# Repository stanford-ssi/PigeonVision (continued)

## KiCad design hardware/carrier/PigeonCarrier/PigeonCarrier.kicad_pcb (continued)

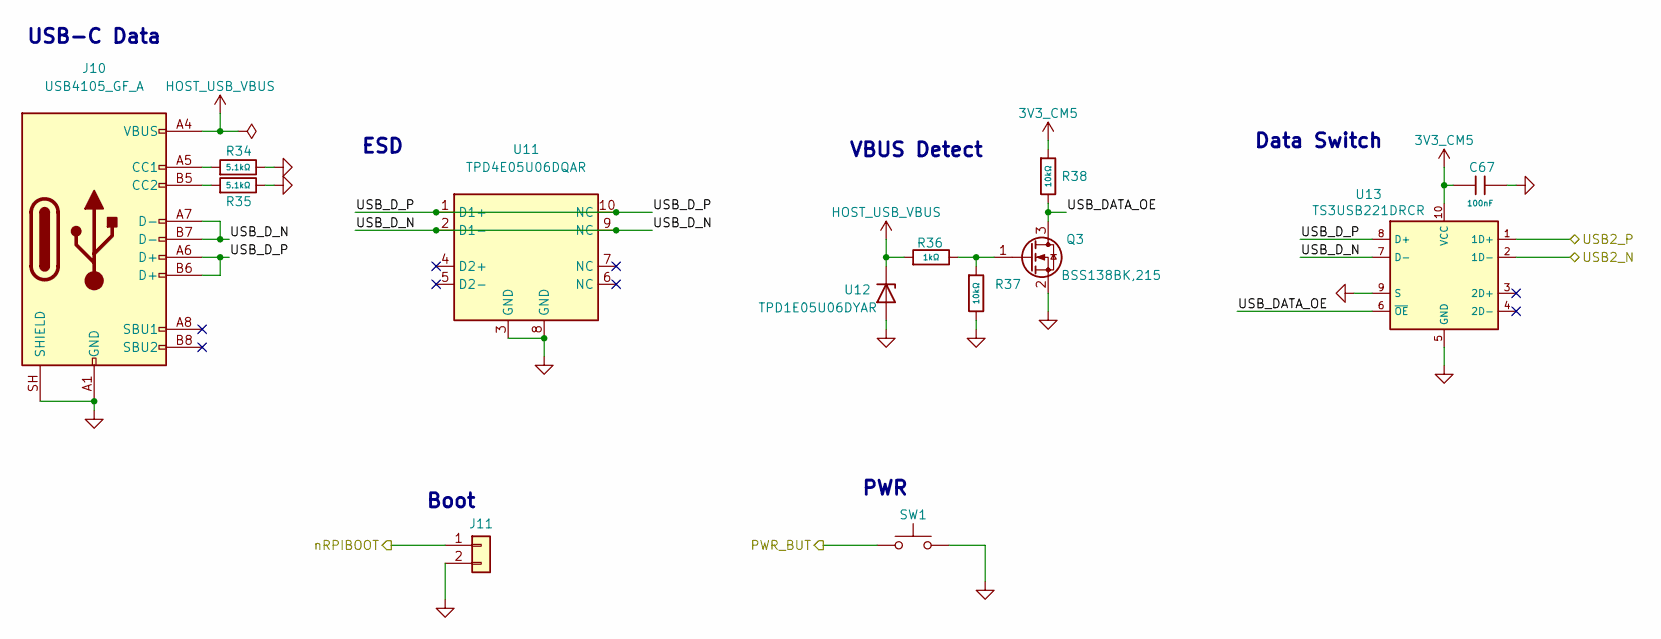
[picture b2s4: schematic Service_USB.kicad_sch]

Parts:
C67: 100nF; C_0402; Voltage Rated 50V; Tolerance ±10%; Part CL05B104KB54PNC; LCSC C307331
J10: USB4105_GF_A; USB_C_Receptacle_GCT_USB4105_GF_A_16P; MPN USB4105-GF-A; DigiKey Part Number 2073-USB4105-GF-ACT-ND
J11: Samtec_TSM-102-01-L-SV-P-TR; Samtec_TSM-102-01_SV_1x02_P2.54mm_SMD; MPN TSM-102-01-L-SV-P-TR; DigiKey Part Number 612-TSM-102-01-L-SV-P-TRCT-ND
Q3: BSS138BK,215; Nexperia_SOT23_BSS138BK; MPN BSS138BK,215; DigiKey Part Number 1727-1141-1-ND
R34, R35: 5.1kΩ; R_0402; Overload Voltage (Max) 50V; Tolerance ±1%; Part 0402WGF5101TCE; LCSC C25905
R36: 1kΩ; R_0402; Overload Voltage (Max) 50V; Tolerance ±1%; Part 0402WGF1001TCE; LCSC C11702
R37, R38: 10kΩ; R_0402; Overload Voltage (Max) 50V; Tolerance ±1%; Part 0402WGF1002TCE; LCSC C25744
SW1: PTS636 SK25 SMTR LFS; CK_PTS636_SK25_SMTR_LFS_GullWing_SMD; MPN PTS636 SK25 SMTR LFS; LCSC C2689642
U11: TPD4E05U06DQAR; TI_DQA0010A_USON-10_1x2.5mm_P0.5mm; MPN TPD4E05U06DQAR; LCSC Part # C138714
U12: TPD1E05U06DYAR; TI_DYA0002A_SOD523_TPD1E05U06; MPN TPD1E05U06DYAR; DigiKey Part # 296-TPD1E05U06DYARCT-ND
U13: TS3USB221DRCR; TI_DRC0010J_VSON-10_3x3mm_P0.5mm; MPN TS3USB221DRCR; DigiKey Part Number 296-21360-1-ND

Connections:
3V3_CM5: C67.1, R38.1, U13.10 (VCC); also elsewhere on the board
/CM5/PWR_BUT: SW1.1; also elsewhere on the board
/CM5/USB2_N: U13.2 (1D-); also elsewhere on the board
/CM5/USB2_P: U13.1 (1D+); also elsewhere on the board
/CM5/nRPIBOOT: J11.1; also elsewhere on the board
/USB & Service/USB_DATA_OE: Q3.3 (D), R38.2, U13.6 (~OE)
/USB & Service/USB_D_N: J10.A7 (D-), J10.B7 (D-), U11.2 (D1-), U11.9 (NC), U13.7 (D-)
/USB & Service/USB_D_P: J10.A6 (D+), J10.B6 (D+), U11.1 (D1+), U11.10 (NC), U13.8 (D+)
GND: C67.2, J10.A1 (GND), J10.A12 (GND), J10.B1 (GND), J10.B12 (GND), J10.SH (SHIELD), J11.2, Q3.2 (S), R34.2, R35.2, R37.2, SW1.2, U11.3 (GND), U11.8 (GND), U12.2 (GND), U13.5 (GND), U13.9 (S), U13.11 (EP); also elsewhere on the board
HOST_USB_VBUS: J10.A4 (VBUS), J10.A9 (VBUS), J10.B4 (VBUS), J10.B9 (VBUS), R36.1, U12.1 (I/O)
unnamed: J10.A5 (CC1), R34.1
unnamed: J10.B5 (CC2), R35.1
unnamed: Q3.1 (G), R36.2, R37.1

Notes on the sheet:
VBUS Detect
Data Switch
USB-C Data
Boot
PWR
ESD

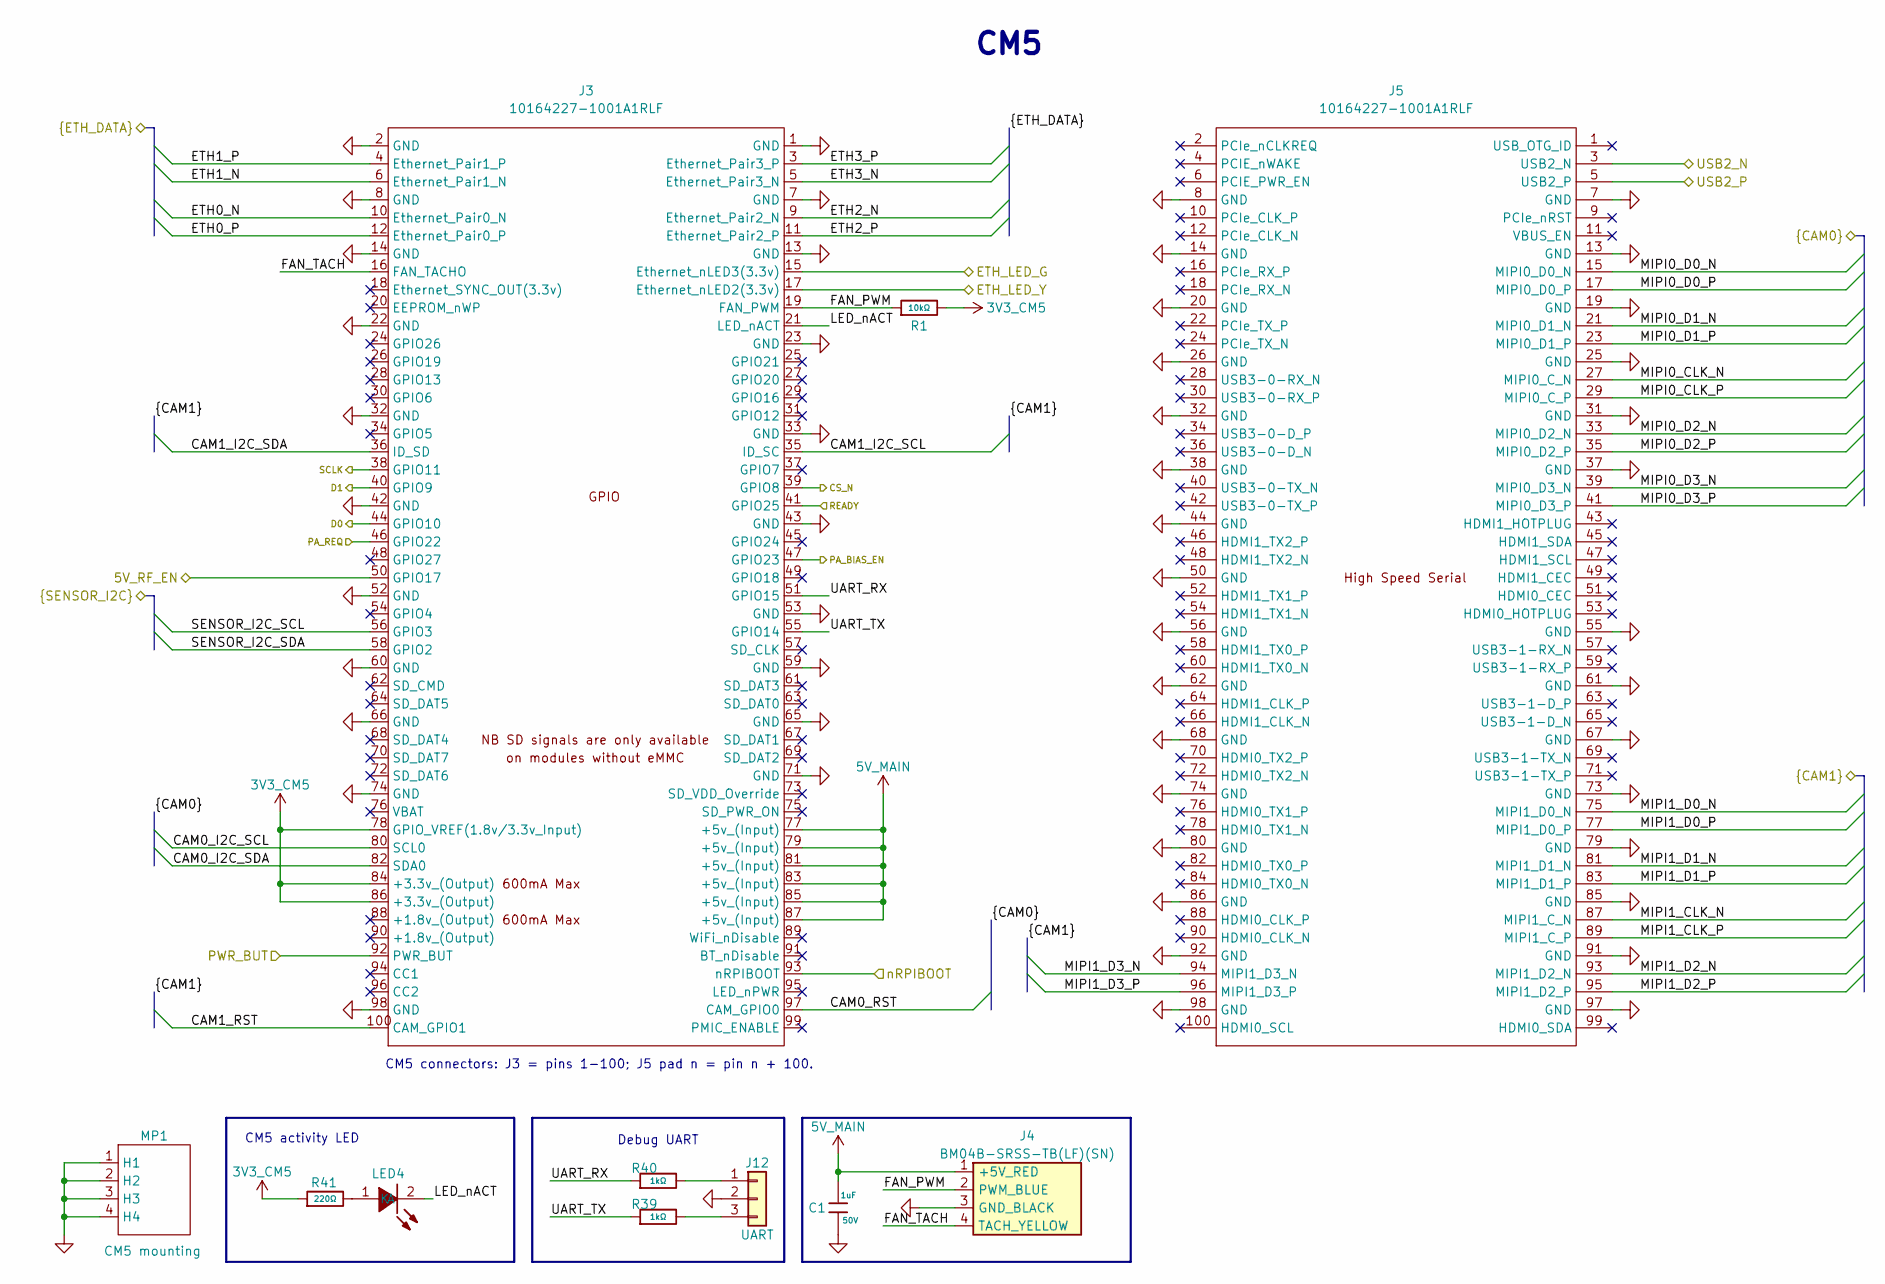
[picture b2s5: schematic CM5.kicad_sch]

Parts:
C1: 1uF; C_0805; Voltage Rated 50V; Tolerance ±10%; Part CL21B105KBFNNNE; LCSC C28323
J3: 10164227-1001A1RLF; Amphenol_10164227-1001A1RLF_2x50_P0.40mm; MPN 10164227-1001A1RLF; LCSC C6782225
J4: BM04B-SRSS-TB(LF)(SN); JST_SH_BM04B-SRSS-TB_1x04-1MP_P1.00mm_Vertical; MPN BM04B-SRSS-TB(LF)(SN); LCSC Part # C160390
J5: 10164227-1001A1RLF; Amphenol_10164227-1001A1RLF_2x50_P0.40mm_CM5_J2; MPN 10164227-1001A1RLF; LCSC C6782225
J12: UART; JST_SH_BM03B-SRSS-TB_1x03-1MP_P1.00mm_Vertical; MPN BM03B-SRSS-TB(LF)(SN); LCSC C160389
LED4: 0805G_Green; Manufacturer Part KT-0805G; LCSC C2297
MP1: CM5 mounting; CM5_Mounting_55x40mm
R1: 10kΩ; R_0402; Overload Voltage (Max) 50V; Tolerance ±1%; Part 0402WGF1002TCE; LCSC C25744
R39, R40: 1kΩ; R_0402; Overload Voltage (Max) 50V; Tolerance ±1%; Part 0402WGF1001TCE; LCSC C11702
R41: 220Ω; R_0402; Overload Voltage (Max) 50V; Tolerance ±1%; Part 0402WGF2200TCE; LCSC C25091

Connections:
3V3_CM5: J3.78 (GPIO_VREF(1.8v/3.3v_Input)), J3.84 (+3.3v_(Output)), J3.86 (+3.3v_(Output)), R1.2, R41.1; also elsewhere on the board
5V_MAIN: C1.1, J3.77 (+5v_(Input)), J3.79 (+5v_(Input)), J3.81 (+5v_(Input)), J3.83 (+5v_(Input)), J3.85 (+5v_(Input)), J3.87 (+5v_(Input)), J4.1 (+5V_RED); also elsewhere on the board
/CM5/5V_RF_EN: J3.50 (GPIO17); also elsewhere on the board
/CM5/CAM0_I2C_SCL: J3.80 (SCL0); also elsewhere on the board
/CM5/CAM0_I2C_SDA: J3.82 (SDA0); also elsewhere on the board
/CM5/CAM0_RST: J3.97 (CAM_GPIO0); also elsewhere on the board
/CM5/CAM1_I2C_SCL: J3.35 (ID_SC); also elsewhere on the board
/CM5/CAM1_I2C_SDA: J3.36 (ID_SD); also elsewhere on the board
/CM5/CAM1_RST: J3.100 (CAM_GPIO1); also elsewhere on the board
/CM5/CS_N: J3.39 (GPIO8); also elsewhere on the board
/CM5/D0: J3.44 (GPIO10); also elsewhere on the board
/CM5/D1: J3.40 (GPIO9); also elsewhere on the board
/CM5/ETH0_N: J3.10 (Ethernet_Pair0_N); also elsewhere on the board
/CM5/ETH0_P: J3.12 (Ethernet_Pair0_P); also elsewhere on the board
/CM5/ETH1_N: J3.6 (Ethernet_Pair1_N); also elsewhere on the board
/CM5/ETH1_P: J3.4 (Ethernet_Pair1_P); also elsewhere on the board
/CM5/ETH2_N: J3.9 (Ethernet_Pair2_N); also elsewhere on the board
/CM5/ETH2_P: J3.11 (Ethernet_Pair2_P); also elsewhere on the board
/CM5/ETH3_N: J3.5 (Ethernet_Pair3_N); also elsewhere on the board
/CM5/ETH3_P: J3.3 (Ethernet_Pair3_P); also elsewhere on the board
/CM5/ETH_LED_G: J3.15 (Ethernet_nLED3(3.3v)); also elsewhere on the board
/CM5/ETH_LED_Y: J3.17 (Ethernet_nLED2(3.3v)); also elsewhere on the board
/CM5/FAN_PWM: J3.19 (FAN_PWM), J4.2 (PWM_BLUE), R1.1
/CM5/FAN_TACH: J3.16 (FAN_TACHO), J4.4 (TACH_YELLOW)
/CM5/LED_nACT: J3.21 (LED_nACT), LED4.2 (K)
/CM5/MIPI0_CLK_N: J5.27 (MIPI0_C_N); also elsewhere on the board
/CM5/MIPI0_CLK_P: J5.29 (MIPI0_C_P); also elsewhere on the board
/CM5/MIPI0_D0_N: J5.15 (MIPI0_D0_N); also elsewhere on the board
/CM5/MIPI0_D0_P: J5.17 (MIPI0_D0_P); also elsewhere on the board
/CM5/MIPI0_D1_N: J5.21 (MIPI0_D1_N); also elsewhere on the board
/CM5/MIPI0_D1_P: J5.23 (MIPI0_D1_P); also elsewhere on the board
/CM5/MIPI0_D2_N: J5.33 (MIPI0_D2_N); also elsewhere on the board
/CM5/MIPI0_D2_P: J5.35 (MIPI0_D2_P); also elsewhere on the board
/CM5/MIPI0_D3_N: J5.39 (MIPI0_D3_N); also elsewhere on the board
/CM5/MIPI0_D3_P: J5.41 (MIPI0_D3_P); also elsewhere on the board
/CM5/MIPI1_CLK_N: J5.87 (MIPI1_C_N); also elsewhere on the board
/CM5/MIPI1_CLK_P: J5.89 (MIPI1_C_P); also elsewhere on the board
/CM5/MIPI1_D0_N: J5.75 (MIPI1_D0_N); also elsewhere on the board
/CM5/MIPI1_D0_P: J5.77 (MIPI1_D0_P); also elsewhere on the board
/CM5/MIPI1_D1_N: J5.81 (MIPI1_D1_N); also elsewhere on the board
/CM5/MIPI1_D1_P: J5.83 (MIPI1_D1_P); also elsewhere on the board
/CM5/MIPI1_D2_N: J5.93 (MIPI1_D2_N); also elsewhere on the board
/CM5/MIPI1_D2_P: J5.95 (MIPI1_D2_P); also elsewhere on the board
/CM5/MIPI1_D3_N: J5.94 (MIPI1_D3_N); also elsewhere on the board
/CM5/MIPI1_D3_P: J5.96 (MIPI1_D3_P); also elsewhere on the board
/CM5/PA_REQ: J3.46 (GPIO22); also elsewhere on the board
/CM5/PWR_BUT: J3.92 (PWR_BUT); also elsewhere on the board
/CM5/READY: J3.41 (GPIO25); also elsewhere on the board
/CM5/SCLK: J3.38 (GPIO11); also elsewhere on the board
/CM5/UART_RX: J3.51 (GPIO15), R40.1
/CM5/UART_TX: J3.55 (GPIO14), R39.1
/CM5/USB2_N: J5.3 (USB2_N); also elsewhere on the board
/CM5/USB2_P: J5.5 (USB2_P); also elsewhere on the board
/CM5/nRPIBOOT: J3.93 (nRPIBOOT); also elsewhere on the board
/PA_BIAS_EN: J3.47 (GPIO23); also elsewhere on the board
/Sensors/SENSOR_I2C_SCL: J3.56 (GPIO3); also elsewhere on the board
/Sensors/SENSOR_I2C_SDA: J3.58 (GPIO2); also elsewhere on the board
GND: C1.2, J3.1 (GND), J3.2 (GND), J3.7 (GND), J3.8 (GND), J3.13 (GND), J3.14 (GND), J3.22 (GND), J3.23 (GND), J3.32 (GND), J3.33 (GND), J3.42 (GND), J3.43 (GND), J3.52 (GND), J3.53 (GND), J3.59 (GND), J3.60 (GND), J3.65 (GND), J3.66 (GND), J3.71 (GND), J3.74 (GND), J3.98 (GND), J4.3 (GND_BLACK), J5.7 (GND), J5.8 (GND), J5.13 (GND), J5.14 (GND), J5.19 (GND), J5.20 (GND), J5.25 (GND), J5.26 (GND), J5.31 (GND), J5.32 (GND), J5.37 (GND), J5.38 (GND), J5.44 (GND), J5.50 (GND), J5.55 (GND), J5.56 (GND), J5.61 (GND), J5.62 (GND), J5.67 (GND), J5.68 (GND), J5.73 (GND), J5.74 (GND), J5.79 (GND), J5.80 (GND), J5.85 (GND), J5.86 (GND), J5.91 (GND), J5.92 (GND), J5.97 (GND), J5.98 (GND), J12.2, MP1.1 (H1), MP1.2 (H2), MP1.3 (H3), MP1.4 (H4); also elsewhere on the board
unnamed: J12.1, R40.2
unnamed: J12.3, R39.2
unnamed: LED4.1 (A), R41.2

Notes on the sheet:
Debug UART
CM5
CM5 connectors: J3 = pins 1-100; J5 pad n = pin n + 100.
CM5 activity LED

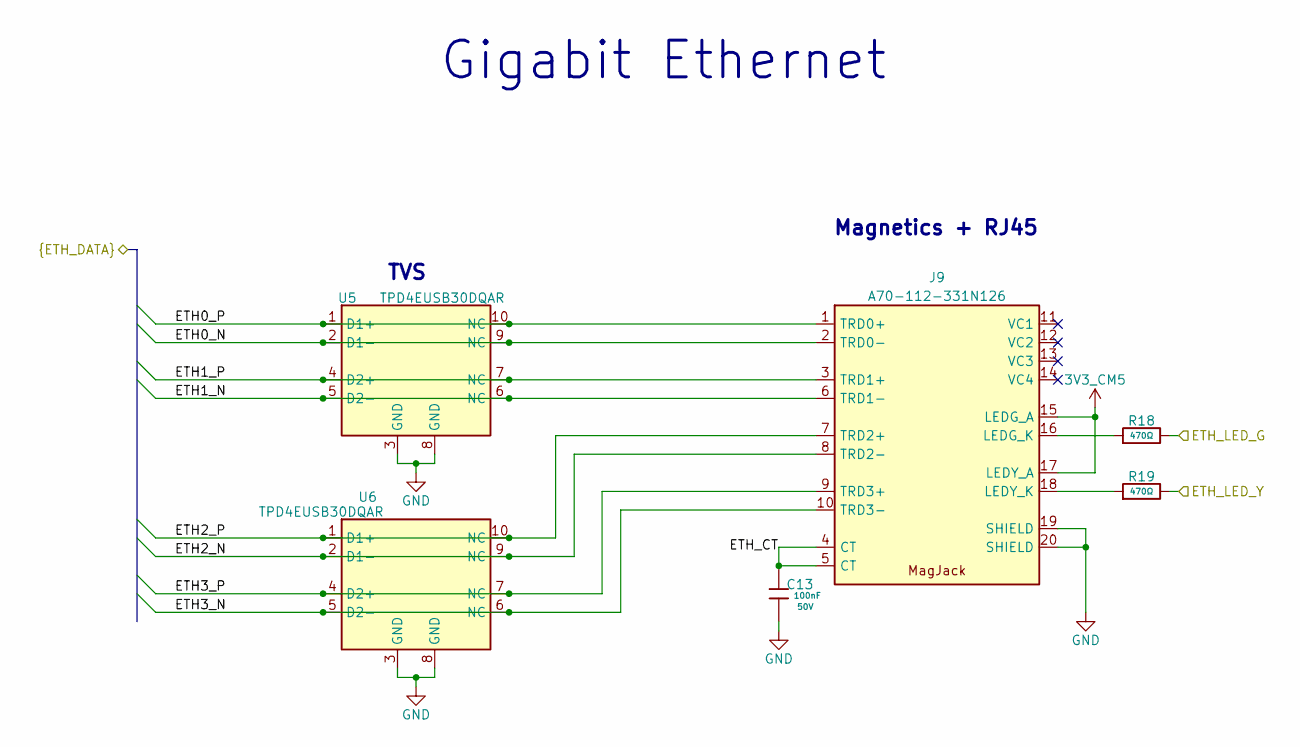
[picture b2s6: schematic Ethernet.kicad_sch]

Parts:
C13: 100nF; C_0402; Voltage Rated 50V; Tolerance ±10%; Part CL05B104KB54PNC; LCSC C307331
J9: A70-112-331N126; RJ45_EDAC_A70-112-331N126; MPN A70-112-331N126; LCSC Part # C43709820
R18, R19: 470Ω; R_0402; Overload Voltage (Max) 50V; Tolerance ±1%; Part 0402WGF4700TCE; LCSC C25117
U5, U6: TPD4EUSB30DQAR; TI_DQA0010A_USON-10_1x2.5mm_P0.5mm; MPN TPD4EUSB30DQAR; LCSC Part # C90627

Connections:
3V3_CM5: J9.15 (LEDG_A), J9.17 (LEDY_A); also elsewhere on the board
/CM5/ETH0_N: J9.2 (TRD0-), U5.2 (D1-), U5.9 (NC); also elsewhere on the board
/CM5/ETH0_P: J9.1 (TRD0+), U5.1 (D1+), U5.10 (NC); also elsewhere on the board
/CM5/ETH1_N: J9.6 (TRD1-), U5.5 (D2-), U5.6 (NC); also elsewhere on the board
/CM5/ETH1_P: J9.3 (TRD1+), U5.4 (D2+), U5.7 (NC); also elsewhere on the board
/CM5/ETH2_N: J9.8 (TRD2-), U6.2 (D1-), U6.9 (NC); also elsewhere on the board
/CM5/ETH2_P: J9.7 (TRD2+), U6.1 (D1+), U6.10 (NC); also elsewhere on the board
/CM5/ETH3_N: J9.10 (TRD3-), U6.5 (D2-), U6.6 (NC); also elsewhere on the board
/CM5/ETH3_P: J9.9 (TRD3+), U6.4 (D2+), U6.7 (NC); also elsewhere on the board
/CM5/ETH_LED_G: R18.2; also elsewhere on the board
/CM5/ETH_LED_Y: R19.2; also elsewhere on the board
/Ethernet/ETH_CT: C13.2, J9.4 (CT), J9.5 (CT)
GND: C13.1, J9.19 (SHIELD), J9.20 (SHIELD), U5.3 (GND), U5.8 (GND), U6.3 (GND), U6.8 (GND); also elsewhere on the board
unnamed: J9.16 (LEDG_K), R18.1
unnamed: J9.18 (LEDY_K), R19.1

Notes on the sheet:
Gigabit Ethernet
TVS
Magnetics + RJ45

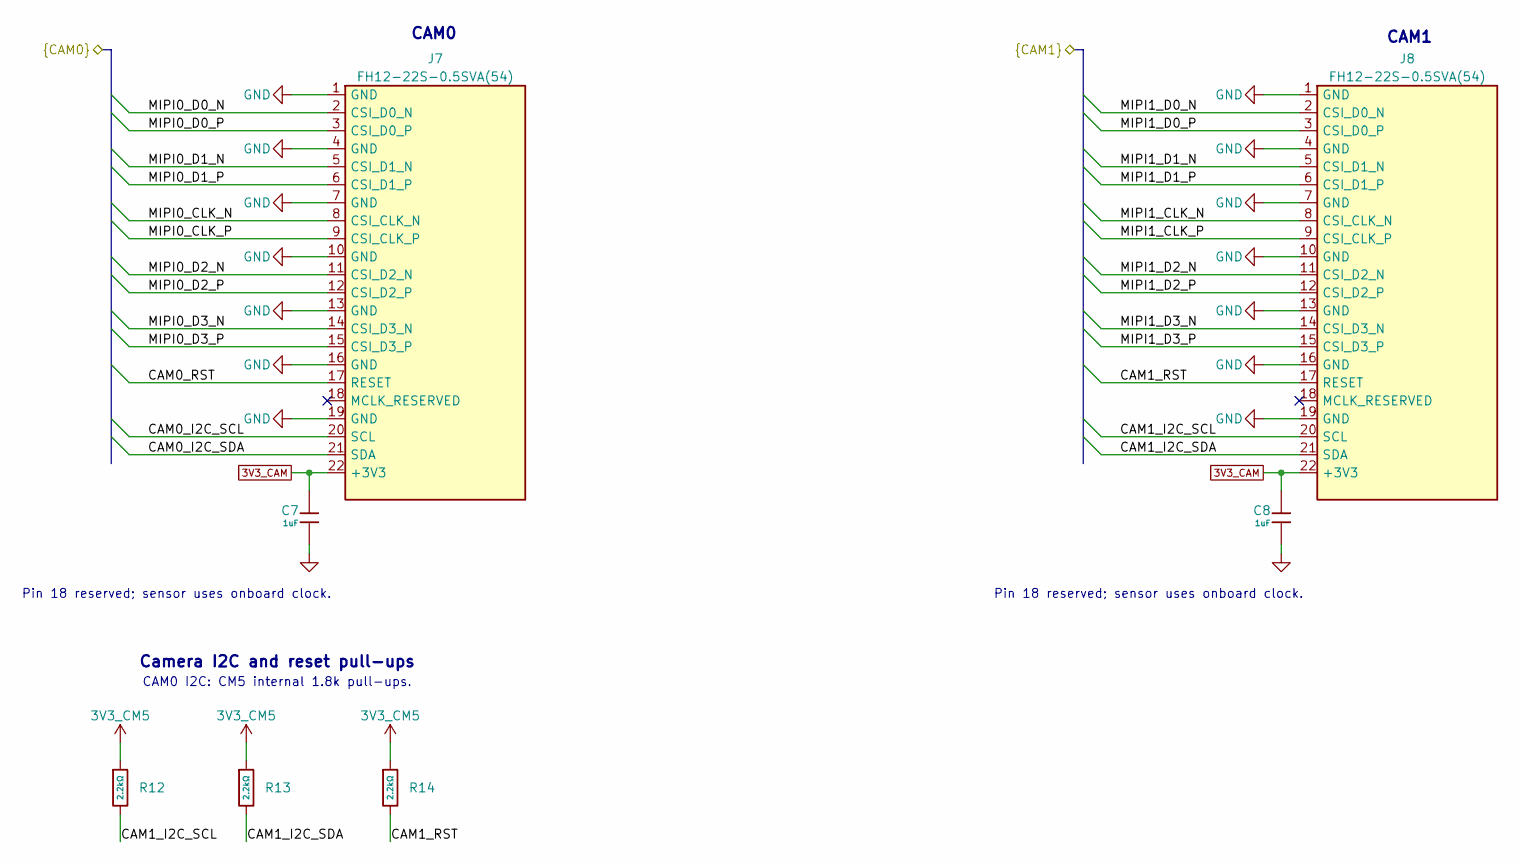
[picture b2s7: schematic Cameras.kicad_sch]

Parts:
C7, C8: 1uF; C_0805; Voltage Rated 50V; Tolerance ±10%; Part CL21B105KBFNNNE; LCSC C28323
J7, J8: FH12-22S-0.5SVA(54); Hirose_FH12-22S-0.5SVA_1x22_P0.50mm_Vertical; MPN FH12-22S-0.5SVA(54); LCSC Part # C6250833
R12, R13, R14: 2.2kΩ; R_0603; Overload Voltage (Max) 75V; Tolerance ±1%; Part 0603WAF2201T5E; LCSC C4190

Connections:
3V3_CAM: C7.1, C8.1, J7.22 (+3V3), J8.22 (+3V3); also elsewhere on the board
3V3_CM5: R12.1, R13.1, R14.1; also elsewhere on the board
/CM5/CAM0_I2C_SCL: J7.20 (SCL); also elsewhere on the board
/CM5/CAM0_I2C_SDA: J7.21 (SDA); also elsewhere on the board
/CM5/CAM0_RST: J7.17 (RESET); also elsewhere on the board
/CM5/CAM1_I2C_SCL: J8.20 (SCL), R12.2; also elsewhere on the board
/CM5/CAM1_I2C_SDA: J8.21 (SDA), R13.2; also elsewhere on the board
/CM5/CAM1_RST: J8.17 (RESET), R14.2; also elsewhere on the board
/CM5/MIPI0_CLK_N: J7.8 (CSI_CLK_N); also elsewhere on the board
/CM5/MIPI0_CLK_P: J7.9 (CSI_CLK_P); also elsewhere on the board
/CM5/MIPI0_D0_N: J7.2 (CSI_D0_N); also elsewhere on the board
/CM5/MIPI0_D0_P: J7.3 (CSI_D0_P); also elsewhere on the board
/CM5/MIPI0_D1_N: J7.5 (CSI_D1_N); also elsewhere on the board
/CM5/MIPI0_D1_P: J7.6 (CSI_D1_P); also elsewhere on the board
/CM5/MIPI0_D2_N: J7.11 (CSI_D2_N); also elsewhere on the board
/CM5/MIPI0_D2_P: J7.12 (CSI_D2_P); also elsewhere on the board
/CM5/MIPI0_D3_N: J7.14 (CSI_D3_N); also elsewhere on the board
/CM5/MIPI0_D3_P: J7.15 (CSI_D3_P); also elsewhere on the board
/CM5/MIPI1_CLK_N: J8.8 (CSI_CLK_N); also elsewhere on the board
/CM5/MIPI1_CLK_P: J8.9 (CSI_CLK_P); also elsewhere on the board
/CM5/MIPI1_D0_N: J8.2 (CSI_D0_N); also elsewhere on the board
/CM5/MIPI1_D0_P: J8.3 (CSI_D0_P); also elsewhere on the board
/CM5/MIPI1_D1_N: J8.5 (CSI_D1_N); also elsewhere on the board
/CM5/MIPI1_D1_P: J8.6 (CSI_D1_P); also elsewhere on the board
/CM5/MIPI1_D2_N: J8.11 (CSI_D2_N); also elsewhere on the board
/CM5/MIPI1_D2_P: J8.12 (CSI_D2_P); also elsewhere on the board
/CM5/MIPI1_D3_N: J8.14 (CSI_D3_N); also elsewhere on the board
/CM5/MIPI1_D3_P: J8.15 (CSI_D3_P); also elsewhere on the board
GND: C7.2, C8.2, J7.1 (GND), J7.4 (GND), J7.7 (GND), J7.10 (GND), J7.13 (GND), J7.16 (GND), J7.19 (GND), J8.1 (GND), J8.4 (GND), J8.7 (GND), J8.10 (GND), J8.13 (GND), J8.16 (GND), J8.19 (GND); also elsewhere on the board

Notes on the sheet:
CAM0 I2C: CM5 internal 1.8k pull-ups.
CAM1
Pin 18 reserved; sensor uses onboard clock.
Camera I2C and reset pull-ups
CAM0

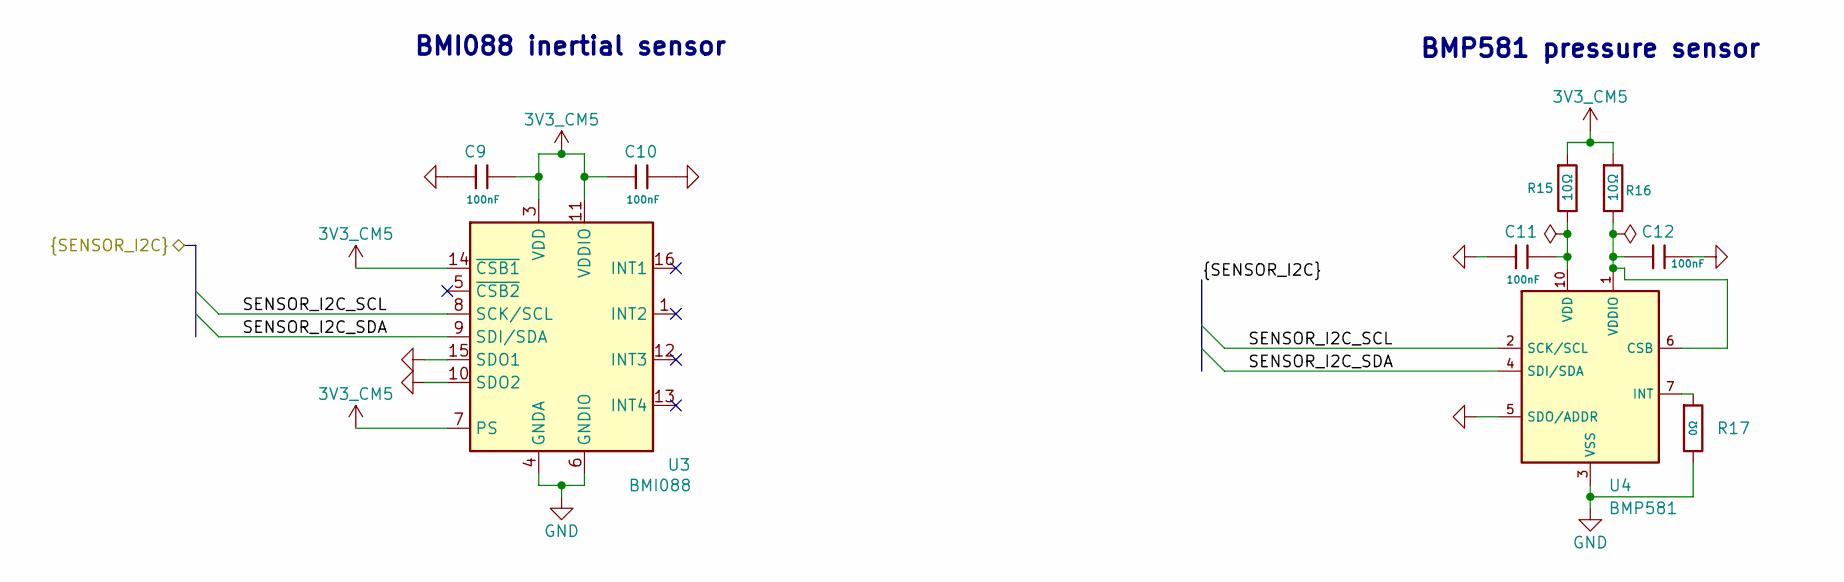
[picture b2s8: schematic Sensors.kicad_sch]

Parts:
C9, C10, C11, C12: 100nF; C_0402; Voltage Rated 50V; Tolerance ±10%; Part CL05B104KB54PNC; LCSC C307331
R15, R16: 10Ω; R_0402; Tolerance ±1%; Overload Voltage (Max) 50V; MPN 0402WGF100JTCE; LCSC Part # C25077
R17: 0Ω; R_0603; Overload Voltage (Max) 75V; Tolerance ±1%; Part 0603WAF0000T5E; LCSC C21189
U3: BMI088; Bosch_LGA-16_4.5x3mm_P0.5mm_LayoutBorder7x1y_ClockwisePinNu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; MPN BMI088; LCSC Part # C194919
U4: BMP581; Bosch_BMP581_LGA-10_2x2mm_P0.5mm; MPN BMP581; LCSC Part # C5362283

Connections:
3V3_CM5: C9.1, C10.2, R15.1, R16.1, U3.3 (VDD), U3.7 (PS), U3.11 (VDDIO), U3.14 (~CSB1); also elsewhere on the board
/Sensors/SENSOR_I2C_SCL: U3.8 (SCK/SCL), U4.2 (SCK/SCL); also elsewhere on the board
/Sensors/SENSOR_I2C_SDA: U3.9 (SDI/SDA), U4.4 (SDI/SDA); also elsewhere on the board
GND: C9.2, C10.1, C11.2, C12.1, R17.2, U3.2 (GNDA), U3.4 (GNDA), U3.6 (GNDIO), U3.10 (SDO2), U3.15 (SDO1), U4.3 (VSS), U4.5 (SDO/ADDR), U4.8 (VSS), U4.9 (VSS); also elsewhere on the board
unnamed: C12.2, R16.2, U4.1 (VDDIO), U4.6 (CSB)
unnamed: R17.1, U4.7 (INT)
unnamed: C11.1, R15.2, U4.10 (VDD)

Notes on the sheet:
BMP581 pressure sensor
BMI088 inertial sensor

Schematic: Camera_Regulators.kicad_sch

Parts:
C55, C56, C61, C62, C63, C64, C65, C66: 10uF; C_1210_3225Metric; Manufacturer Part CL32B106KBJNNNE; LCSC C138687
C57, C58, C59, C60: 100nF; C_0402; Voltage Rated 50V; Tolerance ±10%; Part CL05B104KB54PNC; LCSC C307331
L2: 6.8uH; CYA1040-6_8UH; Manufacturer Part CYA1040-6.8UH; LCSC C6364676
R30: 10kΩ; R_0402; Overload Voltage (Max) 50V; Tolerance ±1%; Part 0402WGF1002TCE; LCSC C25744
R31: 0Ω; R_0402; Overload Voltage (Max) 50V; Tolerance ±1%; Part 0402WGF0000TCE; LCSC C17168
R32: 47kΩ; R_0402; Overload Voltage (Max) 50V; Tolerance ±1%; Part 0402WGF4702TCE; LCSC C25792
R33: 15kΩ; R_0402; Overload Voltage (Max) 50V; Tolerance ±1%; Part 0402WGF1502TCE; LCSC C25756
U10: TPS62933FDRLR; SOT-583-8; MPN TPS62933FDRLR; LCSC Part # C5219272

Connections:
3V3_CAM: C60.2, C61.1, C62.1, C63.1, C64.1, C65.1, C66.1, L2.2, R32.1; also elsewhere on the board
3V3_CM5: R30.2, U10.2 (EN); also elsewhere on the board
GND: C55.2, C56.2, C57.1, C58.1, C60.1, C61.2, C62.2, C63.2, C64.2, C65.2, C66.2, R30.1, R33.2, U10.4 (GND); also elsewhere on the board
unnamed: C59.2, R31.2
unnamed: R31.1, U10.6 (BST)
unnamed: R32.2, R33.1, U10.8 (FB)
unnamed: C58.2, U10.7 (SS)
unnamed: C59.1, L2.1, U10.5 (SW)
VBAT: C55.1, C56.1, C57.2, U10.3 (VIN); also elsewhere on the board

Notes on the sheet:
3.307V Output
F_sw = 500kHz
Random note: Yes this buck is overspecced... im kind of sleepy and am okay with just oversizing the buck for the load right now...
Extra Caps to reduce ripple
t_ss= 14.5ms ~13.4mA
Effective Cap: 56.5uF
~3.05mV ripple W ESR
CALCULATIONS_LINK
VBAT -> 3V3_CAM

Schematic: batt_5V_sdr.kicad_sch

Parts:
C43, C44, C49, C50, C51, C52, C53, C54: 10uF; C_1210_3225Metric; Manufacturer Part CL32B106KBJNNNE; LCSC C138687
C45, C46, C47, C48: 100nF; C_0402; Voltage Rated 50V; Tolerance ±10%; Part CL05B104KB54PNC; LCSC C307331
L1: 6.8uH; CYA1040-6_8UH; Manufacturer Part CYA1040-6.8UH; LCSC C6364676
R25, R29: 10kΩ; R_0402; Overload Voltage (Max) 50V; Tolerance ±1%; Part 0402WGF1002TCE; LCSC C25744
R26: 0Ω; R_0402; Overload Voltage (Max) 50V; Tolerance ±1%; Part 0402WGF0000TCE; LCSC C17168
R27: 51kΩ; R_0402; Overload Voltage (Max) 50V; Tolerance ±1%; Part 0402WGF5102TCE; LCSC C25794
R28: 1.5kΩ; R_0402; Overload Voltage (Max) 50V; Tolerance ±1%; Part 0402WGF1501TCE; LCSC C25867
U9: TPS62933FDRLR; SOT-583-8; MPN TPS62933FDRLR; LCSC Part # C5219272

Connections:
5V_RF: C48.2, C49.1, C50.1, C51.1, C52.1, C53.1, C54.1, L1.2, R27.1; also elsewhere on the board
/CM5/5V_RF_EN: R25.2, U9.2 (EN); also elsewhere on the board
GND: C43.2, C44.2, C45.1, C46.1, C48.1, C49.2, C50.2, C51.2, C52.2, C53.2, C54.2, R25.1, R29.2, U9.4 (GND); also elsewhere on the board
unnamed: C47.2, R26.2
unnamed: R27.2, R28.1
unnamed: R26.1, U9.6 (BST)
unnamed: R28.2, R29.1, U9.8 (FB)
unnamed: C46.2, U9.7 (SS)
unnamed: C47.1, L1.1, U9.5 (SW)
VBAT: C43.1, C44.1, C45.2, U9.3 (VIN); also elsewhere on the board

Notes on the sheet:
CALCULATIONS_LINK
t_ss= 14.5ms ~19mA
Effective Cap: 56.5uF
F_sw = 500kHz
VBAT -> 5V_RF
~4mV ripple W ESR
5.00V Output
Extra Caps to reduce ripple

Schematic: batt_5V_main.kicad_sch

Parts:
C14, C15, C16, C17, C23, C24, C25, C26, C27, C28, C29, C30, C31, C32, C33, C34, C35, C36, C37, C38, C39, C40, C41, C42: 10uF; C_1210_3225Metric; Manufacturer Part CL32B106KBJNNNE; LCSC C138687
C18, C19, C20: 100nF; C_0402; Voltage Rated 50V; Tolerance ±10%; Part CL05B104KB54PNC; LCSC C307331
C21: 1uF; C_0805; Voltage Rated 50V; Tolerance ±10%; Part CL21B105KBFNNNE; LCSC C28323
C22: 33pF; C_0402; Voltage Rated 50V; Tolerance ±5%; Part 0402CG330J500NT; LCSC C1562
L3: 3.3uH; CYA1265-3_3UH; Manufacturer Part CYA1265-3.3UH; LCSC C19268665
R20: 0Ω; R_0402; Overload Voltage (Max) 50V; Tolerance ±1%; Part 0402WGF0000TCE; LCSC C17168
R21: 39kΩ; R_0402; Overload Voltage (Max) 50V; Tolerance ±1%; Part 0402WGF3902TCE; LCSC C25783
R22: 1kΩ; R_0402; Overload Voltage (Max) 50V; Tolerance ±1%; Part 0402WGF1001TCE; LCSC C11702
R23: 10kΩ; R_0402; Overload Voltage (Max) 50V; Tolerance ±1%; Part 0402WGF1002TCE; LCSC C25744
R24: 4.99kΩ; R_0603; Overload Voltage (Max) 75V; Tolerance ±1%; Part 0603WAF4991T5E; LCSC C23046
U7: LM61495RPHR; TI_RPH0016_VQFN-HR-16_3.5x4.5mm; MPN LM61495RPHR; LCSC Part # C2943584

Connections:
5V_MAIN: C23.2, C24.1, C25.2, C26.1, C27.2, C28.1, C29.2, C30.1, C31.2, C32.1, C33.2, C34.1, C35.2, C36.1, C37.2, C38.1, C39.2, C40.1, C41.2, C42.1, L3.2, R21.1, R24.1, U7.5 (BIAS); also elsewhere on the board
/Power & Regulators/VBAT->5V_MAIN/VCC: C21.1, U7.6 (VCC), U7.9 (RT)
GND: C14.2, C15.2, C16.2, C17.2, C18.1, C19.1, C21.2, C23.1, C24.2, C25.1, C26.2, C27.1, C28.2, C29.1, C30.2, C31.1, C32.2, C33.1, C34.2, C35.1, C36.2, C37.1, C38.2, C39.1, C40.2, C41.1, C42.2, R23.2, U7.1 (PGND2), U7.8 (AGND), U7.11 (SPSP), U7.12 (SYNC/MODE), U7.15 (PGND1); also elsewhere on the board
unnamed: C22.1, R24.2
unnamed: R21.2, R22.1
unnamed: C20.1, R20.2, U7.4 (CBOOT)
unnamed: C22.2, R22.2, R23.1, U7.7 (FB)
unnamed: R20.1, U7.3 (RBOOT)
unnamed: C20.2, L3.1, U7.16 (SW)
VBAT: C14.1, C15.1, C16.1, C17.1, C18.2, C19.2, U7.2 (VIN2), U7.13 (EN), U7.14 (VIN1); also elsewhere on the board

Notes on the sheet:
Effective C = 29uF
VBATT = 8.1-12.6V Nominal Voltage = 10.8V
Zero: 107.199 kHz Pole: 371.276 kHz
CALCULATIONS_LINK
I_out = 10A
V_out = 5.0V
Effective C = 180uF
F_sw = 400kHz
Split the caps evenly on for Vin1 and Vin2
VBAT -> 5V_MAIN

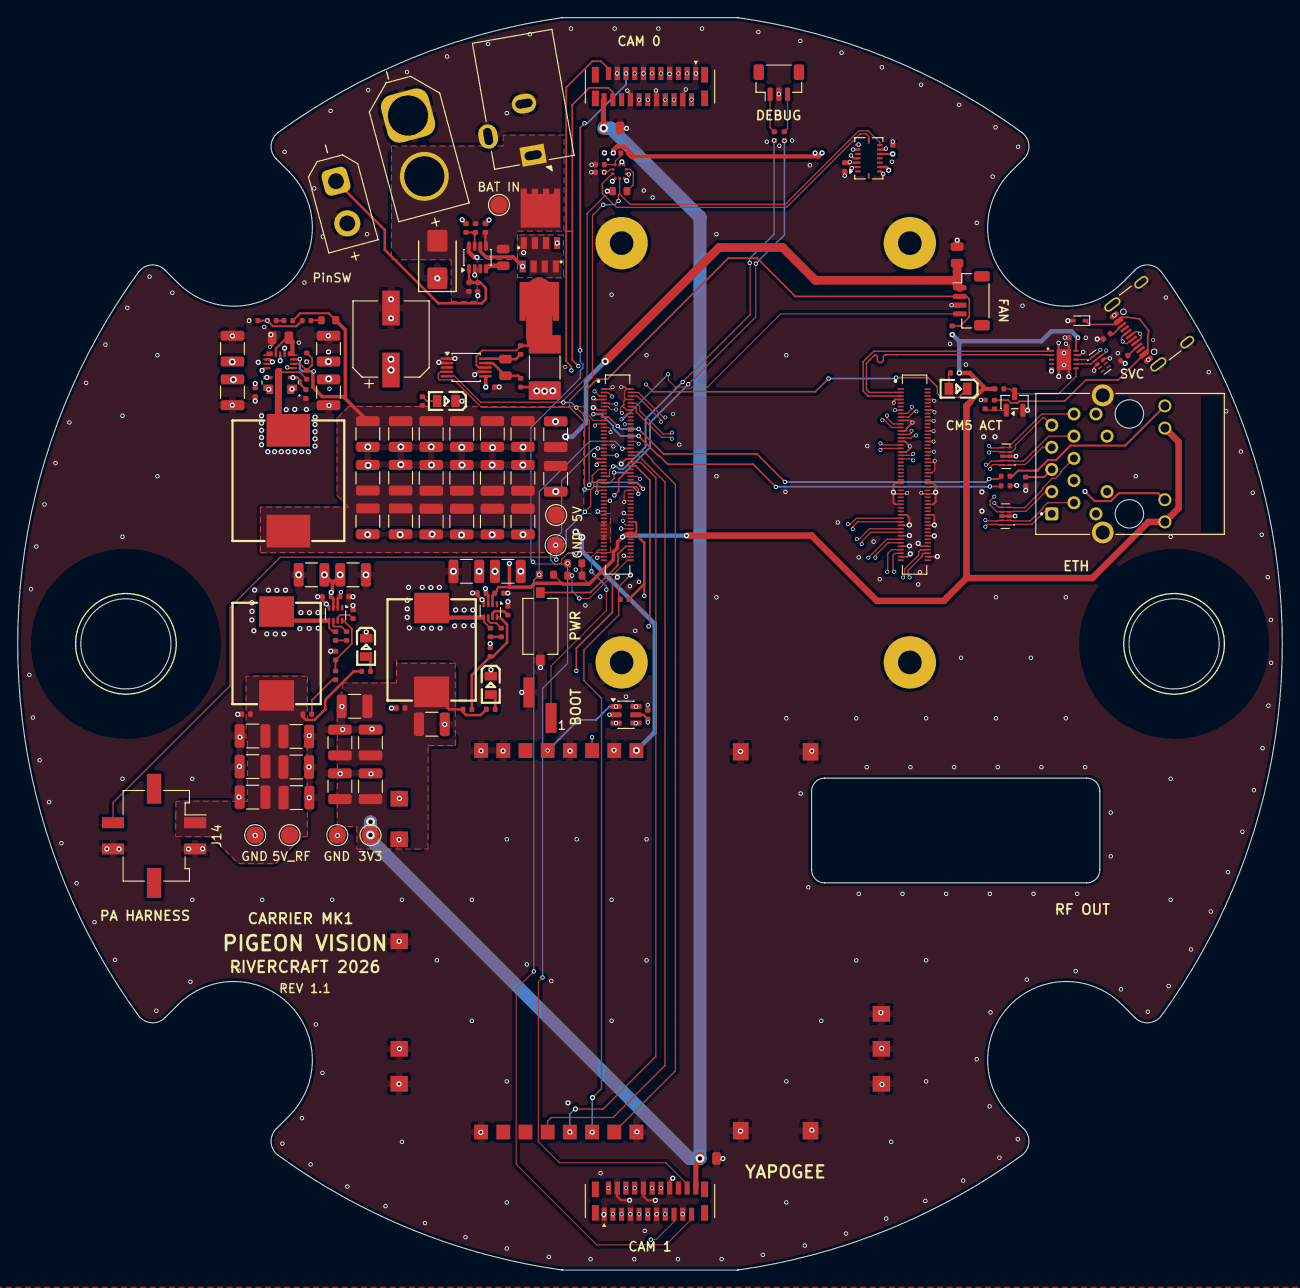
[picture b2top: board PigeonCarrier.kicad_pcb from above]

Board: 6 copper layers, 144.8 x 143.4 mm, 159 parts (0 on the bottom side), 109 nets.

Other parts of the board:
H1, H2: MountingHole_3-8in_Rod_NPTH_10.32mm

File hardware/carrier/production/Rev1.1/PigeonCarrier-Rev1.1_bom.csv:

Designator,Footprint,Quantity,Value,LCSC Part #,Manufacturer,MPN,Assembly,DigiKey Part #
"C1, C21, C5, C7, C8",C_0805,5,1uF,C28323,Samsung Electro-Mechanics,CL21B105KBFNNNE,Top SMT,
"C10, C11, C12, C13, C18, C19, C2, C20, C45, C46, C47, C48, C57, C58, C59, C6, C60, C67, C68, C9",C_0402,20,100nF,C307331,Samsung Electro-Mechanics,CL05B104KB54PNC,Top SMT,
"C14, C15, C16, C17, C23, C24, C25, C26, C27, C28, C29, C30, C31, C32, C33, C34, C35, C36, C37, C38, C39, C40, C41, C42, C43, C44, C49, C50, C51, C52, C53, C54, C55, C56, C61, C62, C63, C64, C65, C66",1210,40,10uF,C138687,Samsung Electro-Mechanics,CL32B106KBJNNNE,Top SMT,
C22,C_0402,1,33pF,C1562,FH(Guangdong Fenghua Advanced Tech),0402CG330J500NT,Top SMT,
C3,C_0805,1,220nF,C5378,Samsung Electro-Mechanics,CL21B224KBFNNNE,Top SMT,
C4,Panasonic_EEE-FK1V221P_CaseF_8x10.2mm,1,220uF,C178562,PANASONIC,EEEFK1V221P,Top SMT,
D1,D_SMB,1,SMBJ18CA,C19077574,hongjiacheng,SMBJ18CA,Top SMT,
J1,AMASS_XT60PB-M_1x02_P7.20mm_Vertical_2025,1,BATT CONN,C19268037,AMASS,XT60PB-M30.G.Y,Through-hole hand solder,
J10,USB_C_Receptacle_GCT_USB4105_GF_A_16P,1,USB4105_GF_A,C3020560,GCT,USB4105-GF-A,Top SMT,
J11,Samtec_TSM-102-01_SV_1x02_P2.54mm_SMD,1,Samtec_TSM-102-01-L-SV-P-TR,C5266181,Samtec,TSM-102-01-L-SV-P-TR,Top SMT,
J12,JST_SH_BM03B-SRSS-TB_1x03-1MP_P1.00mm_Vertical,1,UART,C160389,JST,BM03B-SRSS-TB(LF)(SN),Top SMT,
J14,Molex_Micro-Fit_3.0_43045-0418_2x02-1MP_P3.00mm_Vertical,1,PA HARNESS,,Molex,0430450418,Top SMT,WM1802CT-ND
J2,SameSky_PJ-102AH_Horizontal,1,PJ-102AH,C3096093,Same Sky (formerly CUI Devices),PJ-102AH,Through-hole hand solder,
J3,Amphenol_10164227-1001A1RLF_2x50_P0.40mm,1,10164227-1001A1RLF,C6782225,Amphenol,10164227-1001A1RLF,Top SMT,
J4,JST_SH_BM04B-SRSS-TB_1x04-1MP_P1.00mm_Vertical,1,BM04B-SRSS-TB(LF)(SN),C160390,JST,BM04B-SRSS-TB(LF)(SN),Top SMT,
J5,Amphenol_10164227-1001A1RLF_2x50_P0.40mm_CM5_J2,1,10164227-1001A1RLF,C6782225,Amphenol,10164227-1001A1RLF,Top SMT,
J6,AMASS_XT30UPB-M_1x02_P5.00mm_Vertical_2025,1,PULL_PIN,C428721,AMASS,XT30UPB-M.G.Y,Through-hole hand solder,
"J7, J8",Hirose_FH12-22S-0.5SVA_1x22_P0.50mm_Vertical,2,FH12-22S-0.5SVA(54),C6250833,Hirose,FH12-22S-0.5SVA(54),Top SMT,
J9,RJ45_EDAC_A70-112-331N126,1,A70-112-331N126,C43709820,EDAC,A70-112-331N126,Through-hole hand solder,
"L1, L2",CYA1040-6_8UH,2,6.8uH,C6364676,SHOU HAN,CYA1040-6.8UH,Top SMT,
L3,CYA1265-3_3UH,1,3.3uH,C19268665,SHOU HAN,CYA1265-3.3UH,Top SMT,
"LED1, LED2, LED3, LED4",0805G_Green,4,0805G_Green,C2297,Hubei KENTO Elec,KT-0805G,Top SMT,
"Q1, Q2",TI_CSD18540Q5B_Q5B,2,CSD18540Q5B,C86513,Texas Instruments,CSD18540Q5B,Top SMT,
Q3,Nexperia_SOT23_BSS138BK,1,"BSS138BK,215",C282529,Nexperia,"BSS138BK,215",Top SMT,
"R1, R23, R25, R29, R30, R37, R38",R_0402,7,10kΩ,C25744,UNI-ROYAL(Uniroyal Elec),0402WGF1002TCE,Top SMT,
"R10, R15, R16, R9",R_0402,4,10Ω,C25077,UNI-ROYAL(Uniroyal Elec),0402WGF100JTCE,Top SMT,
"R11, R22, R3, R36, R39, R40, R8",R_0402,7,1kΩ,C11702,UNI-ROYAL(Uniroyal Elec),0402WGF1001TCE,Top SMT,
"R12, R13, R14",R_0603,3,2.2kΩ,C4190,UNI-ROYAL(Uniroyal Elec),0603WAF2201T5E,Top SMT,
R17,R_0603,1,0Ω,C21189,UNI-ROYAL(Uniroyal Elec),0603WAF0000T5E,Top SMT,
"R18, R19",R_0402,2,470Ω,C25117,UNI-ROYAL(Uniroyal Elec),0402WGF4700TCE,Top SMT,
R2,R_0402,1,7.5kΩ,C25918,UNI-ROYAL(Uniroyal Elec),0402WGF7501TCE,Top SMT,
"R20, R26, R28, R31",R_0402,4,0Ω,C17168,UNI-ROYAL(Uniroyal Elec),0402WGF0000TCE,Top SMT,
R21,R_0402,1,39kΩ,C25783,UNI-ROYAL(Uniroyal Elec),0402WGF3902TCE,Top SMT,
R24,R_0603,1,4.99kΩ,C23046,UNI-ROYAL(Uniroyal Elec),0603WAF4991T5E,Top SMT,
R27,R_0402,1,51kΩ,C25794,UNI-ROYAL(Uniroyal Elec),0402WGF5102TCE,Top SMT,
R32,R_0402,1,47kΩ,C25792,UNI-ROYAL(Uniroyal Elec),0402WGF4702TCE,Top SMT,
R33,R_0402,1,15kΩ,C25756,UNI-ROYAL(Uniroyal Elec),0402WGF1502TCE,Top SMT,
"R34, R35",R_0402,2,5.1kΩ,C25905,UNI-ROYAL(Uniroyal Elec),0402WGF5101TCE,Top SMT,
R4,R_0402,1,56kΩ,C25796,UNI-ROYAL(Uniroyal Elec),0402WGF5602TCE,Top SMT,
"R41, R6",R_0402,2,220Ω,C25091,UNI-ROYAL(Uniroyal Elec),0402WGF2200TCE,Top SMT,
"R42, R5",R_0402,2,4.7kΩ,C25900,UNI-ROYAL(Uniroyal Elec),0402WGF4701TCE,Top SMT,
R7,Vishay_WSL2512_5mOhm_2W,1,5mΩ,C844694,Vishay Dale,WSL25125L000FEA18,Top SMT,
SW1,CK_PTS636_SK25_SMTR_LFS_GullWing_SMD,1,PTS636 SK25 SMTR LFS,C2689642,C&K / Littelfuse,PTS636 SK25 SMTR LFS,Top SMT,
U1,Texas_DDF0008A_SOT-8_1.6x2.9mm_P0.65mm,1,LM74502DDFR,C3236215,Texas Instruments,LM74502DDFR,Top SMT,
"U10, U9",SOT-583-8,2,TPS62933FDRLR,C5219272,Texas Instruments,TPS62933FDRLR,Top SMT,
U11,TI_DQA0010A_USON-10_1x2.5mm_P0.5mm,1,TPD4E05U06DQAR,C138714,Texas Instruments,TPD4E05U06DQAR,Top SMT,
U12,TI_DYA0002A_SOD523_TPD1E05U06,1,TPD1E05U06DYAR,C3702980,Texas Instruments,TPD1E05U06DYAR,Top SMT,
U13,TI_DRC0010J_VSON-10_3x3mm_P0.5mm,1,TS3USB221DRCR,C324071,Texas Instruments,TS3USB221DRCR,Top SMT,
U14,SOT-23-6,1,SN74LVC2G17DBVR,C10429,Texas Instruments,SN74LVC2G17DBVR,Top SMT,
U2,TI_DGS0010A_VSSOP-10_3x3mm_P0.5mm,1,INA226AIDGSR,C49851,Texas Instruments,INA226AIDGSR,Top SMT,
U3,Bosch_LGA-16_4.5x3mm_P0.5mm_LayoutBorder7x1y_ClockwisePinNumbering,1,BMI088,C194919,Bosch Sensortec,BMI088,Top SMT,
U4,Bosch_BMP581_LGA-10_2x2mm_P0.5mm,1,BMP581,C5362283,Bosch Sensortec,BMP581,Top SMT,
"U5, U6",TI_DQA0010A_USON-10_1x2.5mm_P0.5mm,2,TPD4EUSB30DQAR,C90627,Texas Instruments,TPD4EUSB30DQAR,Top SMT,
U7,TI_RPH0016_VQFN-HR-16_3.5x4.5mm,1,LM61495RPHR,C2943584,Texas Instruments,LM61495RPHR,Top SMT,
